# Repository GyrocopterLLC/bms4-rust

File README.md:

# bms4-rust
Firmware for a 4-cell modular lithium ion battery management system ("BMS").  
Programmed in Rust.  
## Hardware
The bms4_f051 board.  
Click [hardware](hardware) to see the board design files.  
This board uses an STM32F051K8 microcontroller, and 4 op-amps in a differential amplifier configuration to measure the voltage of 4 batteries stacked in series.

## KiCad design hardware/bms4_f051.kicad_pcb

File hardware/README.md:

# bms4_f051 Hardware Design Files
Designed in Kicad 7.0  
<https://www.kicad.org/>  

## Board Notes
Based on STM32F051K8 microcontroller.  
Uses 2x dual LM2904 op-amps to measure the voltage of the lithium ion batteries. Stepping down the voltage is necessary to avoid damaging the microcontroller's input pins which are limited to 3.3V.
Balancing is performed by 33 ohm shunt resistors, one per cell. The are turned on by the microcontroller through external FETs (AO3400A).
Communication is done through an isolation circuit (ISO7221D). This is used to be able to communicate to other bms4_f051 boards in a series battery configuration. In series, the boards will not share grounds. Connecting one board's ground to another board's ground would create a dangerous short circuit through the LiIon batteries! The boards are designed to be daisy-chained in communication, with the bottom-most (or top-most, your choice) board connected to an external controller, for example an ebike motor controller.

## Board Images

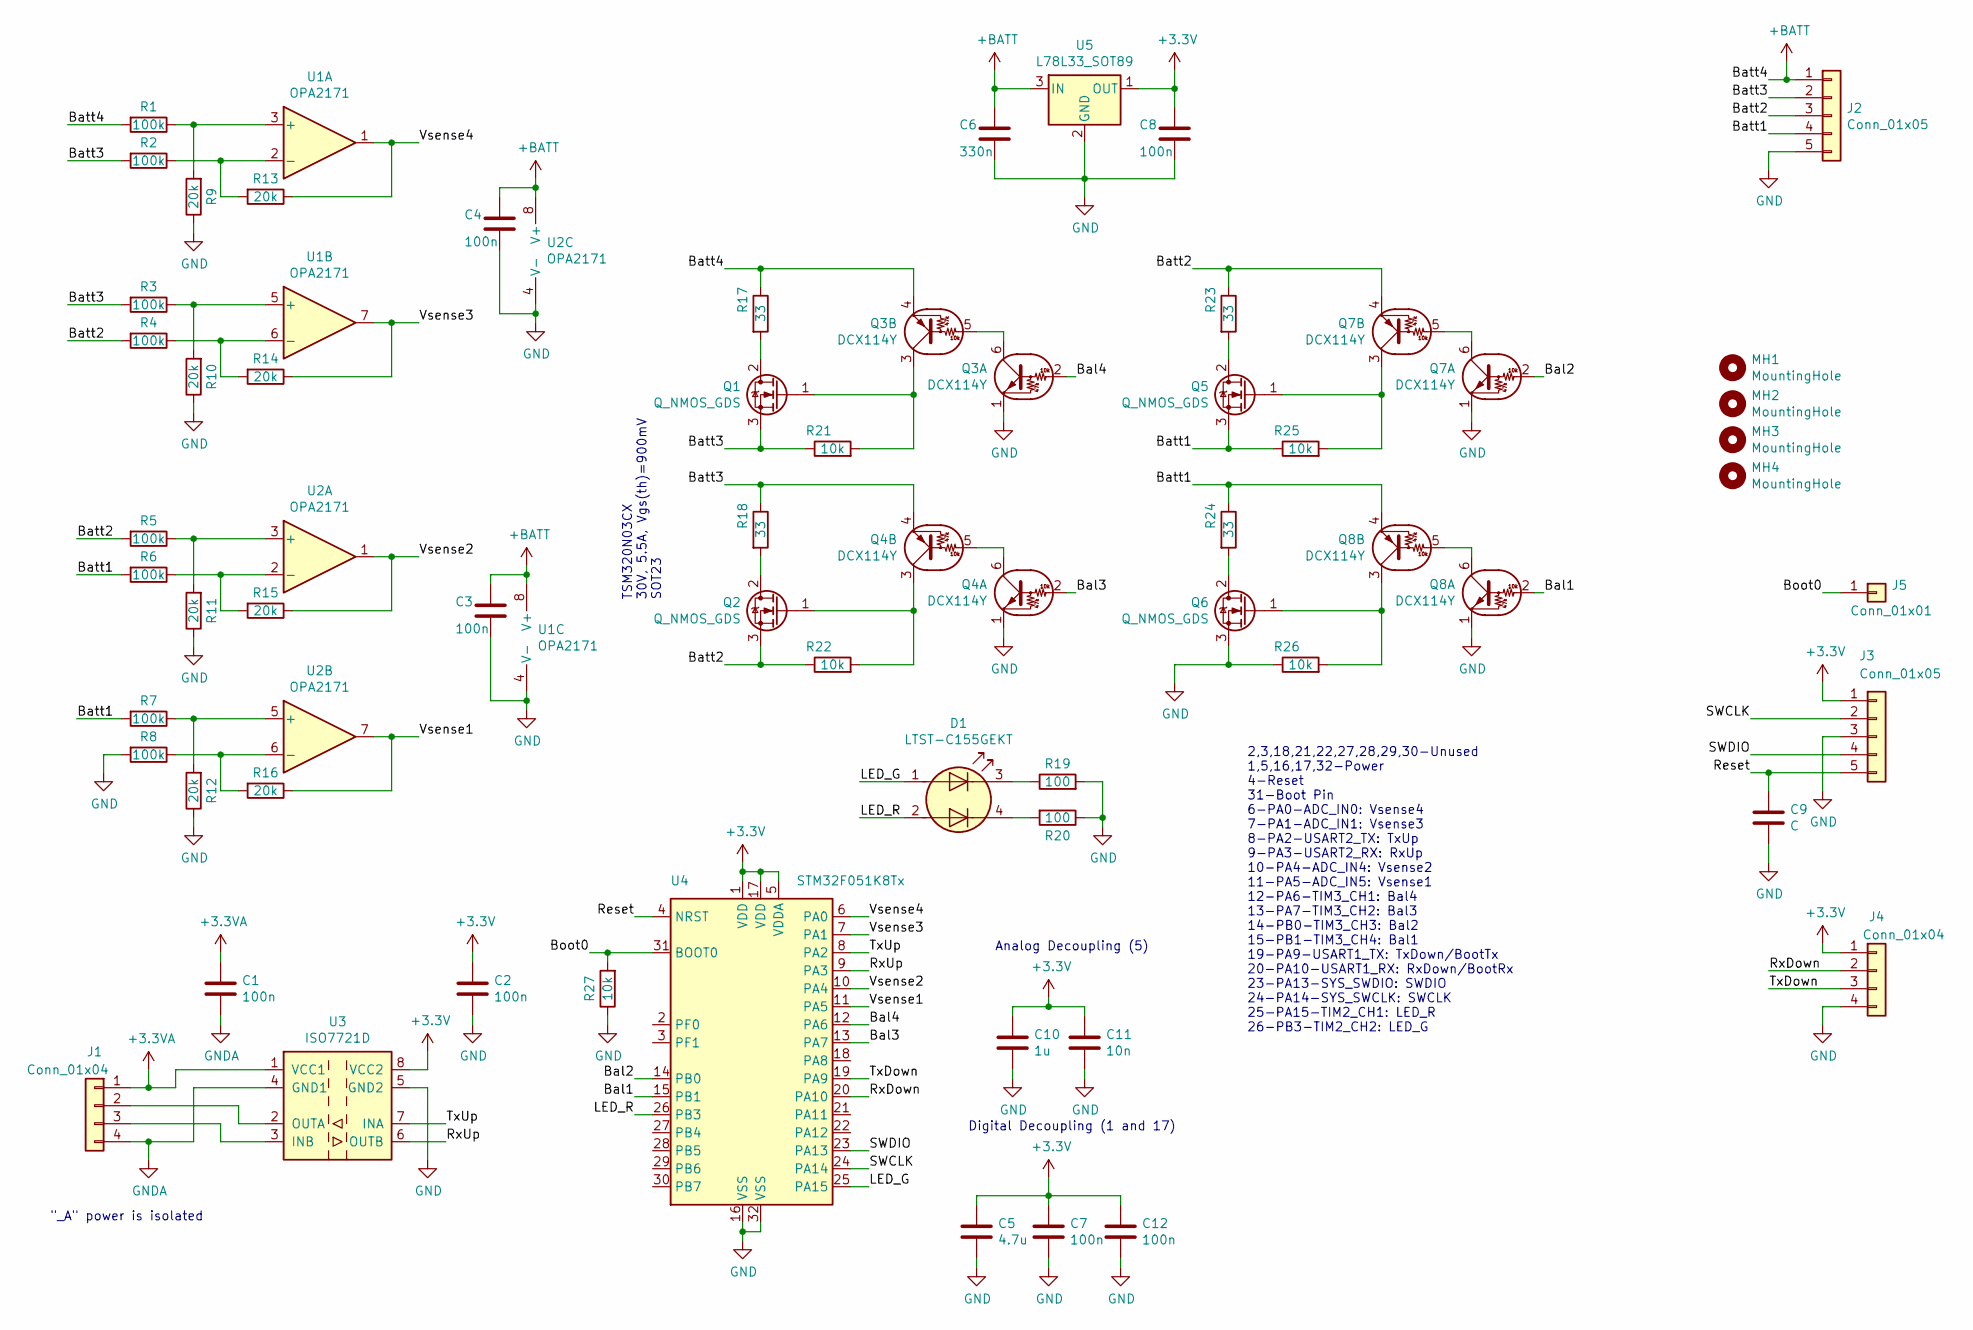
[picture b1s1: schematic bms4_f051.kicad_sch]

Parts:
C1, C2, C7, C8, C12: 100n; C_0603_1608Metric
C3, C4: 100n; C_0805_2012Metric
C5: 4.7u; C_0805_2012Metric
C6: 330n; C_0805_2012Metric
C9: C; C_0603_1608Metric
C10: 1u; C_0603_1608Metric
C11: 10n; C_0603_1608Metric
D1: LTST-C155GEKT
J1, J4: Conn_01x04; JST_XH_B04B-XH-A_1x04_P2.50mm_Vertical
J2: Conn_01x05; JST_XH_B05B-XH-A_1x05_P2.50mm_Vertical
J3: Conn_01x05; PinHeader_1x05_P2.54mm_Vertical
J5: Conn_01x01; PinHeader_1x01_P2.54mm_Vertical
MH1, MH2, MH3, MH4: MountingHole; MountingHole_3.2mm_M3
Q1, Q2, Q5, Q6: Q_NMOS_GDS; SOT-23
Q3, Q4, Q7, Q8: DCX114Y; SOT-363_SC-70-6
R1, R2, R3, R4, R5, R6, R7, R8: 100k; R_0603_1608Metric
R9, R10, R11, R12, R13, R14, R15, R16: 20k; R_0603_1608Metric
R17, R18, R23, R24: 33; R_2512_6332Metric
R19, R20: 100; R_0603_1608Metric
R21, R22, R25, R26, R27: 10k; R_0603_1608Metric
U1, U2: OPA2171; TSSOP-8_3x3mm_P0.65mm
U3: ISO7721D; SOIC-8_3.9x4.9mm_P1.27mm
U4: STM32F051K8Tx; LQFP-32_7x7mm_P0.8mm
U5: L78L33_SOT89; SOT-89-3

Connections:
+3.3VA: C1.1, J1.1, U3.1 (VCC1)
+3V3: C2.1, C5.1, C7.1, C8.1, C10.1, C11.1, C12.1, J3.1, J4.1, U3.8 (VCC2), U4.1 (VDD), U4.5 (VDDA), U4.17 (VDD), U5.1 (OUT)
+BATT: C3.1, C4.1, C6.1, J2.1, Q3.4 (E), R1.2, R17.1, U1.8 (V+), U2.8 (V+), U5.3 (IN)
/Bal1: Q8.2 (B), U4.15 (PB1)
/Bal2: Q7.2 (B), U4.14 (PB0)
/Bal3: Q4.2 (B), U4.13 (PA7)
/Bal4: Q3.2 (B), U4.12 (PA6)
/Batt1: J2.4, Q5.3 (S), Q8.4 (E), R6.2, R7.2, R24.1, R25.1
/Batt2: J2.3, Q2.3 (S), Q7.4 (E), R4.2, R5.2, R22.1, R23.1
/Batt3: J2.2, Q1.3 (S), Q4.4 (E), R2.2, R3.2, R18.1, R21.1
/Boot0: J5.1, R27.2, U4.31 (BOOT0)
/LED_G: D1.1 (A1), U4.25 (PA15)
/LED_R: D1.2 (A2), U4.26 (PB3)
/Reset: C9.1, J3.5, U4.4 (NRST)
/RxDown: J4.2, U4.20 (PA10)
/RxUp: U3.6 (OUTB), U4.9 (PA3)
/SWCLK: J3.2, U4.24 (PA14)
/SWDIO: J3.4, U4.23 (PA13)
/TxDown: J4.3, U4.19 (PA9)
/TxUp: U3.7 (INA), U4.8 (PA2)
/Vsense1: R16.1, U2.7, U4.11 (PA5)
/Vsense2: R15.1, U2.1, U4.10 (PA4)
/Vsense3: R14.1, U1.7, U4.7 (PA1)
/Vsense4: R13.1, U1.1, U4.6 (PA0)
GND: C2.2, C3.2, C4.2, C5.2, C6.2, C7.2, C8.2, C9.2, C10.2, C11.2, C12.2, J2.5, J3.3, J4.4, Q3.1 (E), Q4.1 (E), Q6.3 (S), Q7.1 (E), Q8.1 (E), R8.2, R9.1, R10.1, R11.1, R12.1, R19.2, R20.1, R26.1, R27.1, U1.4 (V-), U2.4 (V-), U3.5 (GND2), U4.16 (VSS), U4.32 (VSS), U5.2 (GND)
GNDA: C1.2, J1.4, U3.4 (GND1)
unnamed: D1.3 (K1), R19.1
unnamed: D1.4 (K2), R20.2
unnamed: J1.2, U3.2 (OUTA)
unnamed: J1.3, U3.3 (INB)
unnamed: Q1.1 (G), Q3.3 (C), R21.2
unnamed: Q1.2 (D), R17.2
unnamed: Q2.1 (G), Q4.3 (C), R22.2
unnamed: Q2.2 (D), R18.2
unnamed: Q3.5 (B), Q3.6 (C)
unnamed: Q4.5 (B), Q4.6 (C)
unnamed: Q5.1 (G), Q7.3 (C), R25.2
unnamed: Q5.2 (D), R23.2
unnamed: Q6.1 (G), Q8.3 (C), R26.2
unnamed: Q6.2 (D), R24.2
unnamed: Q7.5 (B), Q7.6 (C)
unnamed: Q8.5 (B), Q8.6 (C)
unnamed: R1.1, R9.2, U1.3 (+)
unnamed: R3.1, R10.2, U1.5 (+)
unnamed: R5.1, R11.2, U2.3 (+)
unnamed: R7.1, R12.2, U2.5 (+)
unnamed: R2.1, R13.2, U1.2 (-)
unnamed: R4.1, R14.2, U1.6 (-)
unnamed: R6.1, R15.2, U2.2 (-)
unnamed: R8.1, R16.2, U2.6 (-)

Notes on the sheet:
Digital Decoupling (1 and 17)
2,3,18,21,22,27,28,29,30-Unused 1,5,16,17,32-Power 4-Reset 31-Boot Pin 6-PA0-ADC_IN0: Vsense4 7-PA1-ADC_IN1: Vsense3 8-PA2-USART2_TX: TxUp 9-PA3-USART2_RX: RxUp 10-PA4-ADC_IN4: Vsense2 11-PA5-ADC_IN5: Vsense1 12-PA6-TIM3_CH1: Bal4 13-PA7-TIM3_CH2: Bal3 14-PB0-TIM3_CH3: Bal2 15-PB1-TIM3_CH4: Bal1 19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
Analog Decoupling (5)
"_A" power is isolated
TSM320N03CX 30V, 5.5A, Vgs(th)=900mV SOT23

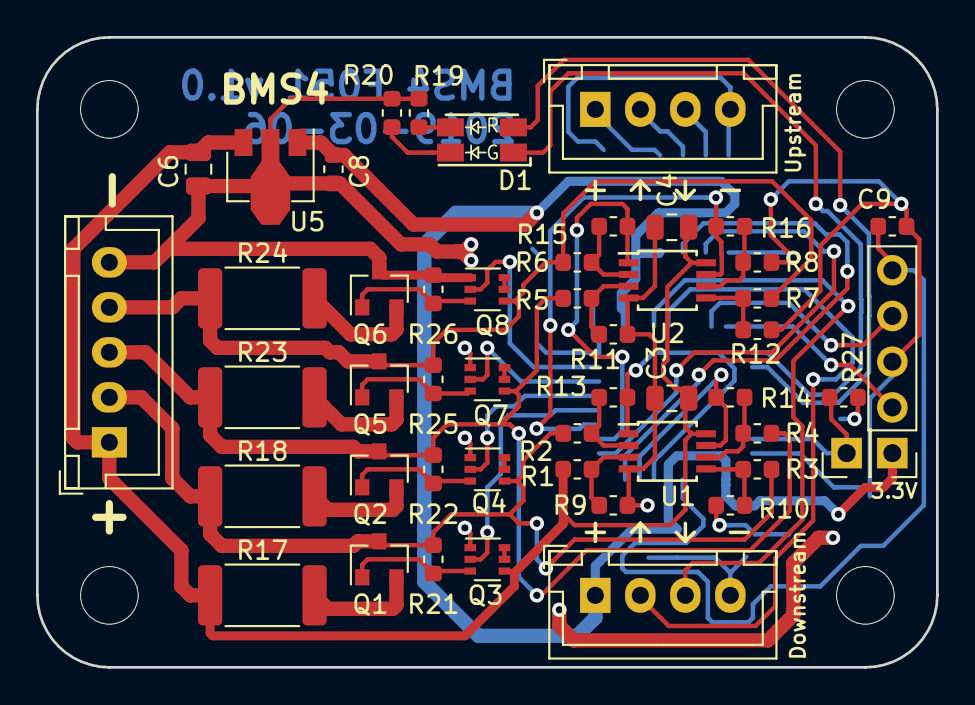
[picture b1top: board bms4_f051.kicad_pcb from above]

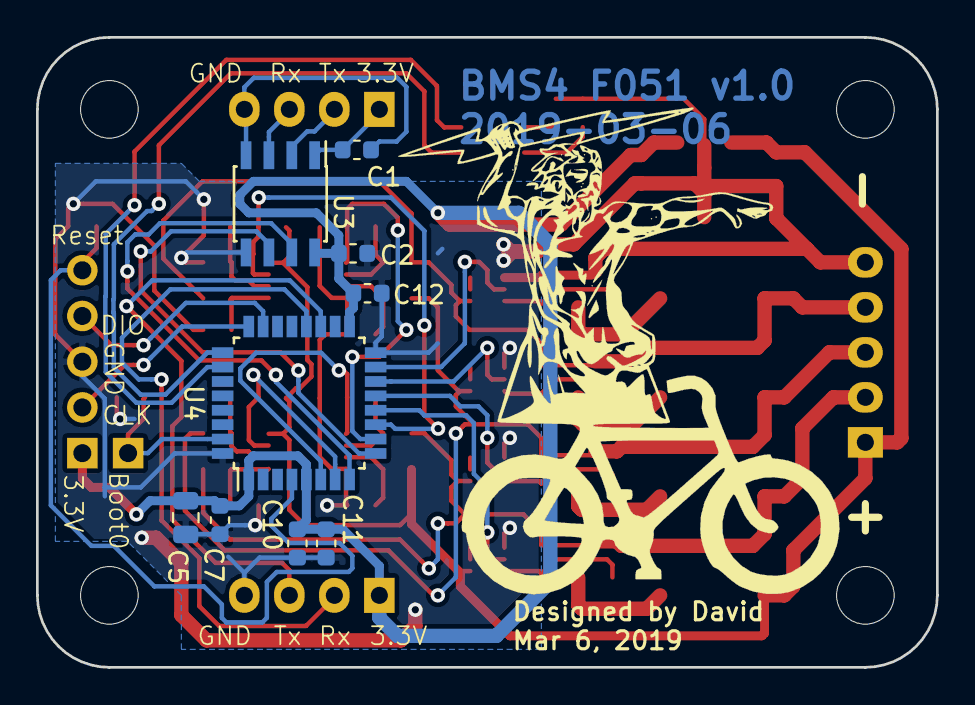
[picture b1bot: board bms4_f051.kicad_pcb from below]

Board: 2 copper layers, 50.0 x 35.0 mm, 62 parts (9 on the bottom side), 50 nets.

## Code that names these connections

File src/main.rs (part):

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mod adc_helper;

struct LEDS{
    green: gpioa::PA15<Output<PushPull>>,
    red: gpiob::PB3<Output<PushPull>>
}

struct AdcPins {
    bat1: gpioa::PA5<Analog>,
    bat2: gpioa::PA4<Analog>,
    bat3: gpioa::PA1<Analog>,
    bat4: gpioa::PA0<Analog>
}

struct ForceSync<T> {
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            let gpioa = p.GPIOA.split(&mut rcc);
            let gpiob = p.GPIOB.split(&mut rcc);

            // (Re-)configure PA15 and PB3 as output
            let mut ledg = gpioa.pa15.into_push_pull_output(cs);
            let mut ledr = gpiob.pb3.into_push_pull_output(cs);

            // Ensure the LEDs are off
            ledg.set_low().ok();
            ledr.set_low().ok();

            // Configure ADC inputs: PA5, 4, 1, and 0 (In1, 2, 3, and 4 respectively)
            let mut in1 = gpioa.pa5.into_analog(cs);
            let mut in2 = gpioa.pa4.into_analog(cs);
            let mut in3 = gpioa.pa1.into_analog(cs);
            let mut in4 = gpioa.pa0.into_analog(cs);
            
            // let mut madc = Adc::new(p.ADC, &mut rcc);
            //let mut madc = HelpfulAdc::new(p.ADC, &mut rcc.regs);
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
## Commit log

2023-11-08 Initial hardware and software - software is just a stub
2023-11-08 fixed image links in hardware readme
2023-11-13 ADC tested working in blocking mode
2023-11-20 continued working on adc
